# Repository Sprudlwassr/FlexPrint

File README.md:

\# Diploma thesis FlexPrint

This diploma thesis develops a modular CoreXY 3D printer that flexibly combines mechanics, electronics, and software and is designed for future extensions. The mechanical setup includes a Z-axis with four individually driven motors, linear rails, and a magnetically interchangeable toolhead system for different nozzle diameters. Electronically, a custom mainboard based on ESP32 or STM32 with TMC2209 stepper motor drivers is implemented. Control is provided via customized firmware (Klipper or Marlin). Extensions such as alternative toolheads, modular interfaces, and a secure power supply are integrated. The goal is a practical, reliable 3D printer that goes beyond commercial devices and serves as a platform for research and development.

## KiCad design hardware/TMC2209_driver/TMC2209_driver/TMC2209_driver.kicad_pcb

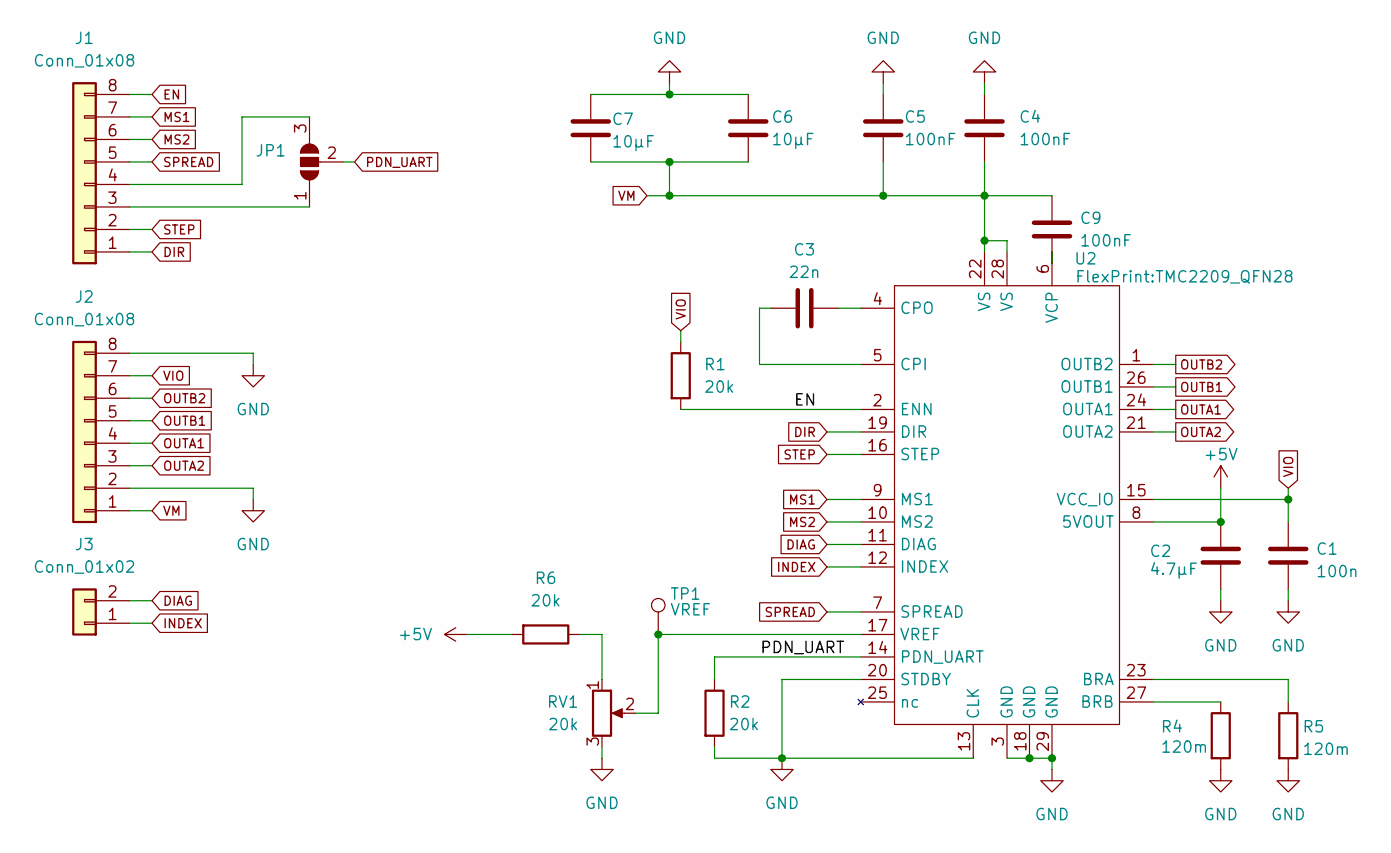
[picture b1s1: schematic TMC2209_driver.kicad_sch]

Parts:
C1: 100n; C_0402_1005Metric
C2: 4.7µF; C_0402_1005Metric
C3: 22n; C_0402_1005Metric
C4, C5, C9: 100nF; C_0402_1005Metric
C6, C7: 10µF; C_1206_3216Metric
J1, J2: Conn_01x08; PinHeader_1x08_P2.54mm_Vertical
J3: Conn_01x02; PinHeader_1x02_P2.54mm_Vertical
JP1: SolderJumper_3_Open; SolderJumper_3Pads
R1, R2, R6: 20k; R_0402_1005Metric
R4, R5: 120m; R_0805_2012Metric
RV1: 20k; TRIMMER_3312J-1-203E
TP1: VREF; TestPoint_Pad_D1.0mm
U2: TMC2209_QFN28

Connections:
+5V: C2.1, R6.2, U2.8 (5VOUT)
DIAG: J3.2, U2.11 (DIAG)
DIR: J1.1, U2.19 (DIR)
EN: J1.8, R1.2, U2.2 (ENN)
GND: C1.2, C2.2, C4.1, C5.1, C6.1, C7.1, J2.2, J2.8, R2.2, R4.2, R5.2, RV1.3, U2.3 (GND), U2.13 (CLK), U2.18 (GND), U2.20 (STDBY), U2.29 (GND)
INDEX: J3.1, U2.12 (INDEX)
MS1: J1.7, U2.9 (MS1)
MS2: J1.6, U2.10 (MS2)
unnamed: J1.3, JP1.1 (A)
unnamed: J1.4, JP1.3 (B)
unnamed: R6.1, RV1.1
unnamed: R5.1, U2.23 (BRA)
unnamed: R4.1, U2.27 (BRB)
unnamed: C3.1, U2.5 (CPI)
unnamed: C3.2, U2.4 (CPO)
unnamed: C9.2, U2.6 (VCP)
unnamed: RV1.2, TP1.1, U2.17 (VREF)
OUTA1: J2.4, U2.24 (OUTA1)
OUTA2: J2.3, U2.21 (OUTA2)
OUTB1: J2.5, U2.26 (OUTB1)
OUTB2: J2.6, U2.1 (OUTB2)
PDN_UART: JP1.2 (C), R2.1, U2.14 (PDN_UART)
SPREAD: J1.5, U2.7 (SPREAD)
STEP: J1.2, U2.16 (STEP)
VIO: C1.1, J2.7, R1.1, U2.15 (VCC_IO)
VM: C4.2, C5.2, C6.2, C7.2, C9.1, J2.1, U2.22 (VS), U2.28 (VS)

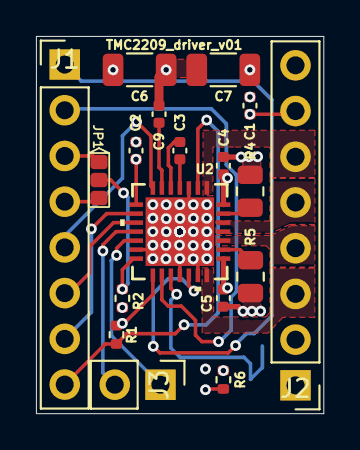
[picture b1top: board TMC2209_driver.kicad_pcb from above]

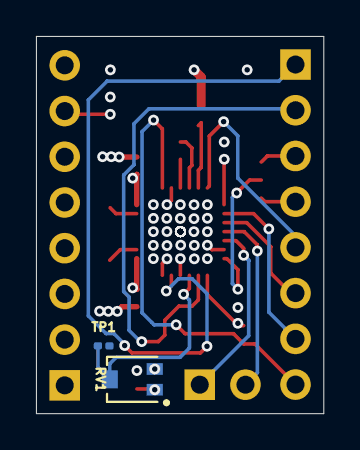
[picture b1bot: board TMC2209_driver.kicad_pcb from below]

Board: 4 copper layers, 16.0 x 21.0 mm, 20 parts (2 on the bottom side), 26 nets.

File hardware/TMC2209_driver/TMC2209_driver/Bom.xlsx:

Pos | Sourced | Placed | References | Value | Footprint | Stk | Stk Gesamt | Preis pro stk | Preis ab 10stk | Gesamtpreise | Anzahl Boards
1 | https://www.reichelt.at/at/de/shop/produkt/mlcc_0402_100nf_5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 | no | C3, C4, C5, C9 | 100nF | C_0402_1005Metric | 4 | 40 | 0.02 | 0.02 | 0.8 | 10
2 | https://www.reichelt.at/at/de/shop/produkt/mlcc_1206_10_f_35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 | no | C6, C7 | 10µF | C_1206_3216Metric | 2 | 20 | 0.08 | 0.08 | 1.6
3 | https://www.reichelt.at/at/de/shop/produkt/mlcc_0402_4_7uf_1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 | no | C2 | 4.7µF | C_0402_1005Metric | 1 | 10 | 0.03 | 0.03 | 0.3
4 | https://www.reichelt.at/at/de/shop/produkt/mlcc_0402_22nf_50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 | no | C3 | 22n | C_0402_1005Metric | 1 | 10 | 0.02 | 0.02 | 0.2
5 | https://www.reichelt.at/at/de/shop/produkt/smd-widerstand_04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 | no | R1, R2, R6 | 20k | R_0402_1005Metric | 3 | 30 | 0.02 | 0.02 | 0.6
6 | https://www.mouser.at/ProductDetail/Panasonic/ERJ-6BSFR12V?q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 | no | R4, R5 | 120m | R_0805_2012Metric | 2 | 20 | 0.24099999999999999 | 0.155 | 3.1
7 | https://www.reichelt.at/at/de/shop/produkt/tmc2209_schrittmo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 | no | U2 | ~ | TMC2209_QFN28 | 1 | 10 | 3.33 | 3.33 | 33.299999999999997
8 | https://www.mouser.at/ProductDetail/Bourns/TC42X-2-203E?qs=A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 | no | RV1 | 20k | TC42X-2-203E | 1 | 10 | 0.38700000000000001 | 0.28999999999999998 | 2.9
9 |  | no | J1, J2 | Conn_01x08 | PinHeader_1x08_P2.54mm_Vertical | 2 | 20
10 |  | no | J3 | Conn_01x02 | PinHeader_1x02_P2.54mm_Vertical | 1 | 10
 |  |  |  |  |  |  |  |  | Summe | 42.8

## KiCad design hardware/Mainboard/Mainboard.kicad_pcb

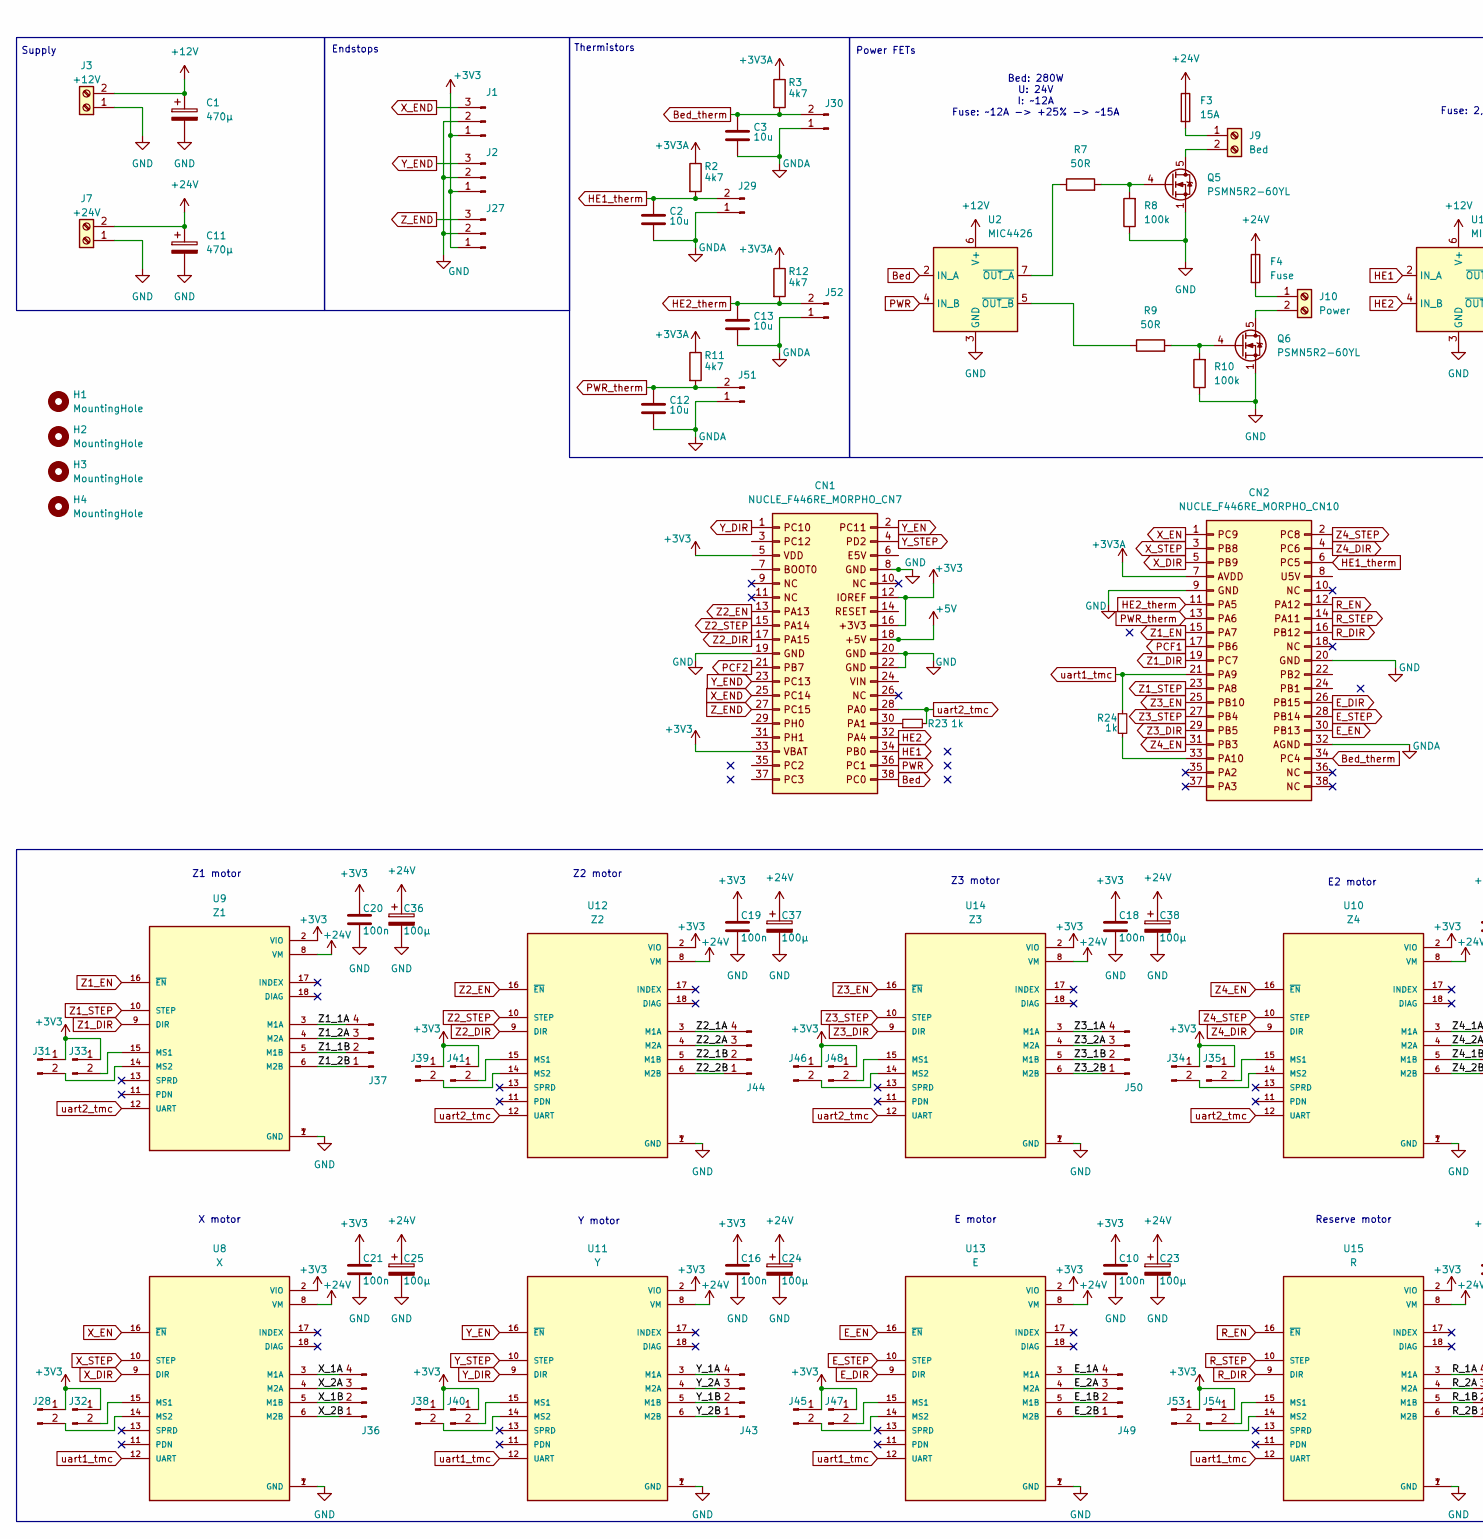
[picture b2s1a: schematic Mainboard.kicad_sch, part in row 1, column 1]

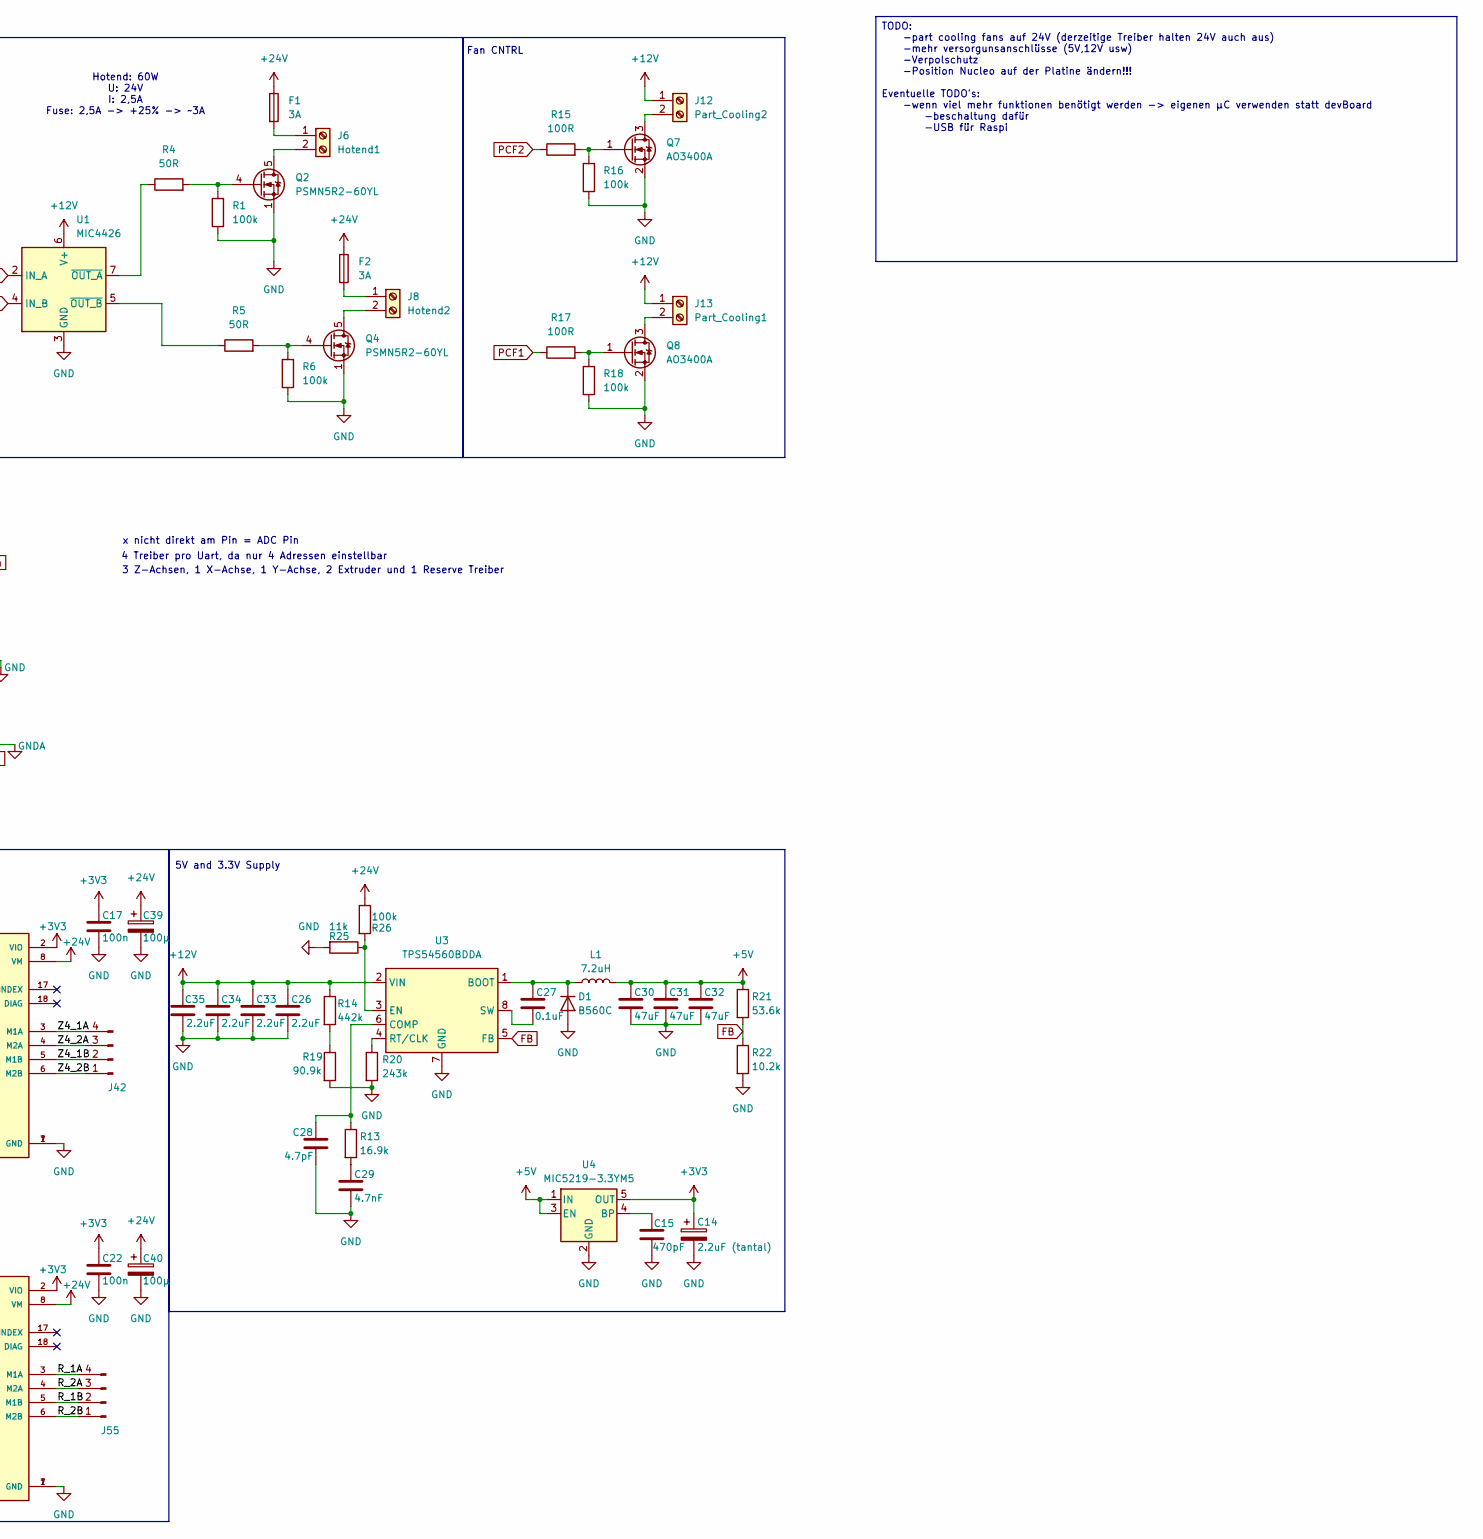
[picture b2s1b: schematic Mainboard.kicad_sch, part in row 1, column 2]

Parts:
C1, C11: 470µ; CP_Elec_16x17.5
C2, C3, C12, C13: 10u; C_0805_2012Metric
C10, C16, C17, C18, C19, C20, C21, C22: 100n; C_0805_2012Metric
C14: 2.2uF (tantal); CP_EIA-3216-10_Kemet-I
C15: 470pF; C_0805_2012Metric
C23, C24, C25, C36, C37, C38, C39, C40: 100µ; CP_Elec_8x10
C26, C33, C34, C35: 2.2uF; C_0805_2012Metric
C27: 0.1uF; C_0805_2012Metric
C28: 4.7pF; C_0805_2012Metric
C29: 4.7nF; C_0805_2012Metric
C30, C31, C32: 47uF; C_0805_2012Metric
CN1: NUCLE_F446RE_MORPHO_CN7; PinSocket_2x19_P2.54mm_Vertical
CN2: NUCLE_F446RE_MORPHO_CN10; PinSocket_2x19_P2.54mm_Vertical
D1: B560C; D_SMC
F1, F2: 3A; Fuse_1206_3216Metric
F3: 15A; Fuse_1206_3216Metric
F4: Fuse; Fuse_1206_3216Metric
H1, H2, H3, H4: MountingHole; MountingHole_2.7mm_M2.5_Pad_Via
J1: X_END; JST_XH_B3B-XH-A_1x03_P2.50mm_Vertical
J2: Y_END; JST_XH_B3B-XH-A_1x03_P2.50mm_Vertical
J3: +12V; TerminalBlock_bornier-2_P5.08mm
J6: Hotend1; TerminalBlock_bornier-2_P5.08mm
J7: +24V; TerminalBlock_bornier-2_P5.08mm
J8: Hotend2; TerminalBlock_bornier-2_P5.08mm
J9: Bed; TerminalBlock_bornier-2_P5.08mm
J10: Power; TerminalBlock_bornier-2_P5.08mm
J12: Part_Cooling2; JST_XH_B2B-XH-A_1x02_P2.50mm_Vertical
J13: Part_Cooling1; JST_XH_B2B-XH-A_1x02_P2.50mm_Vertical
J27: Z_END; JST_XH_B3B-XH-A_1x03_P2.50mm_Vertical
J28: X_MS2; PinHeader_1x02_P2.54mm_Vertical
J29: HE1_therm; JST_XH_B2B-XH-A_1x02_P2.50mm_Vertical
J30: Bed_therm; JST_XH_B2B-XH-A_1x02_P2.50mm_Vertical
J31: Z1_MS2; PinHeader_1x02_P2.54mm_Vertical
J32: X_MS1; PinHeader_1x02_P2.54mm_Vertical
J33: Z1_MS1; PinHeader_1x02_P2.54mm_Vertical
J34: Z4_MS2; PinHeader_1x02_P2.54mm_Vertical
J35: Z4_MS1; PinHeader_1x02_P2.54mm_Vertical
J36: X_Motor; PinHeader_1x04_P2.54mm_Vertical
J37: Z1_Motor; PinHeader_1x04_P2.54mm_Vertical
J38: Y_MS2; PinHeader_1x02_P2.54mm_Vertical
J39: Z2_MS2; PinHeader_1x02_P2.54mm_Vertical
J40: Y_MS1; PinHeader_1x02_P2.54mm_Vertical
J41: Z2_MS1; PinHeader_1x02_P2.54mm_Vertical
J42: Z4_Motor; PinHeader_1x04_P2.54mm_Vertical
J43: Y_Motor; PinHeader_1x04_P2.54mm_Vertical
J44: Z2_Motor; PinHeader_1x04_P2.54mm_Vertical
J45: E_MS2; PinHeader_1x02_P2.54mm_Vertical
J46: Z3_MS2; PinHeader_1x02_P2.54mm_Vertical
J47: E_MS1; PinHeader_1x02_P2.54mm_Vertical
J48: Z3_MS1; PinHeader_1x02_P2.54mm_Vertical
J49: E_Motor; PinHeader_1x04_P2.54mm_Vertical
J50: Z3_Motor; PinHeader_1x04_P2.54mm_Vertical
J51: PWR_therm; JST_XH_B2B-XH-A_1x02_P2.50mm_Vertical
J52: HE2_therm; JST_XH_B2B-XH-A_1x02_P2.50mm_Vertical
J53: R_MS2; PinHeader_1x02_P2.54mm_Vertical
J54: R_MS1; PinHeader_1x02_P2.54mm_Vertical
J55: R_Motor; PinHeader_1x04_P2.54mm_Vertical
L1: 7.2uH; L_Wuerth_WE-PDF
Q2, Q4, Q5, Q6: PSMN5R2-60YL; LFPAK56
Q7, Q8: AO3400A; SOT-23
R1, R6, R8, R10, R16, R18, R26: 100k; R_0805_2012Metric
R2, R3, R11, R12: 4k7; R_0805_2012Metric
R4, R5, R7, R9: 50R; R_0805_2012Metric
R13: 16.9k; R_0805_2012Metric
R14: 442k; R_0805_2012Metric
R15, R17: 100R; R_0805_2012Metric
R19: 90.9k; R_0805_2012Metric
R20: 243k; R_0805_2012Metric
R21: 53.6k; R_0805_2012Metric
R22: 10.2k; R_0805_2012Metric
R23, R24: 1k; R_0805_2012Metric
R25: 11k; R_0805_2012Metric
U1, U2: MIC4426; SOIC-8_3.9x4.9mm_P1.27mm
U3: TPS54560BDDA; Texas_R-PDSO-G8_EP2.95x4.9mm_Mask2.4x3.1mm_ThermalVias
U4: MIC5219-3.3YM5; SOT-23-5
U8: X; MODULE_TMC2209_SILENTSTEPSTICK; PARTREV 1.20
U9: Z1; MODULE_TMC2209_SILENTSTEPSTICK; PARTREV 1.20
U10: Z4; MODULE_TMC2209_SILENTSTEPSTICK; PARTREV 1.20
U11: Y; MODULE_TMC2209_SILENTSTEPSTICK; PARTREV 1.20
U12: Z2; MODULE_TMC2209_SILENTSTEPSTICK; PARTREV 1.20
U13: E; MODULE_TMC2209_SILENTSTEPSTICK; PARTREV 1.20
U14: Z3; MODULE_TMC2209_SILENTSTEPSTICK; PARTREV 1.20
U15: R; MODULE_TMC2209_SILENTSTEPSTICK; PARTREV 1.20

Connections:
+3V3: C10.1, C14.1, C16.1, C17.1, C18.1, C19.1, C20.1, C21.1, C22.1, CN1.5, CN1.12, CN1.16, CN1.33, J1.1, J2.1, J27.1, J28.1, J31.1, J32.1, J33.1, J34.1, J35.1, J38.1, J39.1, J40.1, J41.1, J45.1, J46.1, J47.1, J48.1, J53.1, J54.1, U4.5 (OUT), U8.2 (VIO), U9.2 (VIO), U10.2 (VIO), U11.2 (VIO), U12.2 (VIO), U13.2 (VIO), U14.2 (VIO), U15.2 (VIO)
+3V3A: CN2.7, R2.1, R3.1, R11.1, R12.1
+5V: C30.1, C31.1, C32.1, CN1.18, L1.2, R21.1, U4.1 (IN), U4.3 (EN)
+12V: C1.1, C26.1, C33.1, C34.1, C35.1, J3.2, J12.1, J13.1, R14.1, U1.6 (V+), U2.6 (V+), U3.2 (VIN)
+24V: C11.1, C23.1, C24.1, C25.1, C36.1, C37.1, C38.1, C39.1, C40.1, F1.1, F2.1, F3.1, F4.1, J7.2, R26.1, U8.8 (VM), U9.8 (VM), U10.8 (VM), U11.8 (VM), U12.8 (VM), U13.8 (VM), U14.8 (VM), U15.8 (VM)
/E_1A: J49.4, U13.3 (M1A)
/E_1B: J49.2, U13.5 (M1B)
/E_2A: J49.3, U13.4 (M2A)
/E_2B: J49.1, U13.6 (M2B)
/R_1A: J55.4, U15.3 (M1A)
/R_1B: J55.2, U15.5 (M1B)
/R_2A: J55.3, U15.4 (M2A)
/R_2B: J55.1, U15.6 (M2B)
/X_1A: J36.4, U8.3 (M1A)
/X_1B: J36.2, U8.5 (M1B)
/X_2A: J36.3, U8.4 (M2A)
/X_2B: J36.1, U8.6 (M2B)
/Y_1A: J43.4, U11.3 (M1A)
/Y_1B: J43.2, U11.5 (M1B)
/Y_2A: J43.3, U11.4 (M2A)
/Y_2B: J43.1, U11.6 (M2B)
/Z1_1A: J37.4, U9.3 (M1A)
/Z1_1B: J37.2, U9.5 (M1B)
/Z1_2A: J37.3, U9.4 (M2A)
/Z1_2B: J37.1, U9.6 (M2B)
/Z2_1A: J44.4, U12.3 (M1A)
/Z2_1B: J44.2, U12.5 (M1B)
/Z2_2A: J44.3, U12.4 (M2A)
/Z2_2B: J44.1, U12.6 (M2B)
/Z3_1A: J50.4, U14.3 (M1A)
/Z3_1B: J50.2, U14.5 (M1B)
/Z3_2A: J50.3, U14.4 (M2A)
/Z3_2B: J50.1, U14.6 (M2B)
/Z4_1A: J42.4, U10.3 (M1A)
/Z4_1B: J42.2, U10.5 (M1B)
/Z4_2A: J42.3, U10.4 (M2A)
/Z4_2B: J42.1, U10.6 (M2B)
Bed: CN1.38, U2.2 (IN_A)
Bed_therm: C3.1, CN2.34, J30.2, R3.2
E_DIR: CN2.26, U13.9 (DIR)
E_EN: CN2.30, U13.16 (~EN)
E_STEP: CN2.28, U13.10 (STEP)
FB: R21.2, R22.1, U3.5 (FB)
GND: C1.2, C10.2, C11.2, C14.2, C15.2, C16.2, C17.2, C18.2, C19.2, C20.2, C21.2, C22.2, C23.2, C24.2, C25.2, C26.2, C28.2, C29.2, C30.2, C31.2, C32.2, C33.2, C34.2, C35.2, C36.2, C37.2, C38.2, C39.2, C40.2, CN1.8, CN1.19, CN1.20, CN1.22, CN2.9, CN2.20, D1.2 (A), J1.2, J2.2, J3.1, J7.1, J27.2, Q2.1 (S), Q2.2 (S), Q2.3 (S), Q4.1 (S), Q4.2 (S), Q4.3 (S), Q5.1 (S), Q5.2 (S), Q5.3 (S), Q6.1 (S), Q6.2 (S), Q6.3 (S), Q7.2 (S), Q8.2 (S), R1.1, R6.1, R8.1, R10.1, R16.1, R18.1, R19.2, R20.2, R22.2, R25.2, U1.3 (GND), U2.3 (GND), U3.7 (GND), U3.9 (GND), U4.2 (GND), U8.1 (GND), U8.7 (GND), U9.1 (GND), U9.7 (GND), U10.1 (GND), U10.7 (GND), U11.1 (GND), U11.7 (GND), U12.1 (GND), U12.7 (GND), U13.1 (GND), U13.7 (GND), U14.1 (GND), U14.7 (GND), U15.1 (GND), U15.7 (GND)
GNDA: C2.2, C3.2, C12.2, C13.2, CN2.32, J29.1, J30.1, J51.1, J52.1
HE1: CN1.34, U1.2 (IN_A)
HE1_therm: C2.1, CN2.6, J29.2, R2.2
HE2: CN1.32, U1.4 (IN_B)
HE2_therm: C13.1, CN2.11, J52.2, R12.2
unnamed: C29.1, R13.2
unnamed: CN1.30, R23.1
unnamed: CN2.33, R24.2
unnamed: C27.1, D1.1 (K), L1.1, U3.1 (BOOT)
unnamed: F1.2, J6.1
unnamed: J6.2, Q2.5 (D)
unnamed: F2.2, J8.1
unnamed: J8.2, Q4.5 (D)
unnamed: F3.2, J9.1
unnamed: J9.2, Q5.5 (D)
unnamed: F4.2, J10.1
unnamed: J10.2, Q6.5 (D)
unnamed: J12.2, Q7.3 (D)
unnamed: J13.2, Q8.3 (D)
unnamed: J28.2, U8.14 (MS2)
unnamed: J31.2, U9.14 (MS2)
unnamed: J32.2, U8.15 (MS1)
unnamed: J33.2, U9.15 (MS1)
unnamed: J34.2, U10.14 (MS2)
unnamed: J35.2, U10.15 (MS1)
unnamed: J38.2, U11.14 (MS2)
unnamed: J39.2, U12.14 (MS2)
unnamed: J40.2, U11.15 (MS1)
unnamed: J41.2, U12.15 (MS1)
unnamed: J45.2, U13.14 (MS2)
unnamed: J46.2, U14.14 (MS2)
unnamed: J47.2, U13.15 (MS1)
unnamed: J48.2, U14.15 (MS1)
unnamed: J53.2, U15.14 (MS2)
unnamed: J54.2, U15.15 (MS1)
unnamed: Q2.4 (G), R1.2, R4.2
unnamed: Q4.4 (G), R5.2, R6.2
unnamed: Q5.4 (G), R7.2, R8.2
unnamed: Q6.4 (G), R9.2, R10.2
unnamed: Q7.1 (G), R15.2, R16.2
unnamed: Q8.1 (G), R17.2, R18.2
unnamed: R14.2, R19.1
unnamed: R4.1, U1.7 (~OUT_A)
unnamed: R5.1, U1.5 (~OUT_B)
unnamed: R7.1, U2.7 (~OUT_A)
unnamed: R9.1, U2.5 (~OUT_B)
unnamed: C28.1, R13.1, U3.6 (COMP)
unnamed: R25.1, R26.2, U3.3 (EN)
unnamed: R20.1, U3.4 (RT/CLK)
unnamed: C27.2, U3.8 (SW)
unnamed: C15.1, U4.4 (BP)
PCF1: CN2.17, R17.1
PCF2: CN1.21, R15.1
PWR: CN1.36, U2.4 (IN_B)
PWR_therm: C12.1, CN2.13, J51.2, R11.2
R_DIR: CN2.16, U15.9 (DIR)
R_EN: CN2.12, U15.16 (~EN)
R_STEP: CN2.14, U15.10 (STEP)
X_DIR: CN2.5, U8.9 (DIR)
X_EN: CN2.1, U8.16 (~EN)
X_END: CN1.25, J1.3
X_STEP: CN2.3, U8.10 (STEP)
Y_DIR: CN1.1, U11.9 (DIR)
Y_EN: CN1.2, U11.16 (~EN)
Y_END: CN1.23, J2.3
Y_STEP: CN1.4, U11.10 (STEP)
Z1_DIR: CN2.19, U9.9 (DIR)
Z1_EN: CN2.15, U9.16 (~EN)
Z1_STEP: CN2.23, U9.10 (STEP)
Z2_DIR: CN1.17, U12.9 (DIR)
Z2_EN: CN1.13, U12.16 (~EN)
Z2_STEP: CN1.15, U12.10 (STEP)
Z3_DIR: CN2.29, U14.9 (DIR)
Z3_EN: CN2.25, U14.16 (~EN)
Z3_STEP: CN2.27, U14.10 (STEP)
Z4_DIR: CN2.4, U10.9 (DIR)
Z4_EN: CN2.31, U10.16 (~EN)
Z4_STEP: CN2.2, U10.10 (STEP)
Z_END: CN1.27, J27.3
uart1_tmc: CN2.21, R24.1, U8.12 (UART), U11.12 (UART), U13.12 (UART), U15.12 (UART)
uart2_tmc: CN1.28, R23.2, U9.12 (UART), U10.12 (UART), U12.12 (UART), U14.12 (UART)

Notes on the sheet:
x nicht direkt am Pin = ADC Pin
Y motor
5V and 3.3V Supply
Hotend: 60W U: 24V I: 2,5A Fuse: 2,5A -> +25% -> ~3A
Reserve motor
Z3 motor
Supply
Z2 motor
E motor
Endstops
E2 motor
Bed: 280W U: 24V I: ~12A Fuse: ~12A -> +25% -> ~15A
4 Treiber pro Uart, da nur 4 Adressen einstellbar
Power FETs
Thermistors
Fan CNTRL
Z1 motor
3 Z-Achsen, 1 X-Achse, 1 Y-Achse, 2 Extruder und 1 Reserve Treiber
X motor
TODO: -part cooling fans auf 24V (derzeitige Treiber halten 24V auch aus) -mehr versorgunsanschlüsse (5V,12V usw) -Verpolschutz -Position Nucleo auf der Platine ändern!!! Eventuelle TODO's: -wenn viel mehr funktionen benötigt werden -> eigenen µC verwenden statt devBoard -beschaltung dafür -USB für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

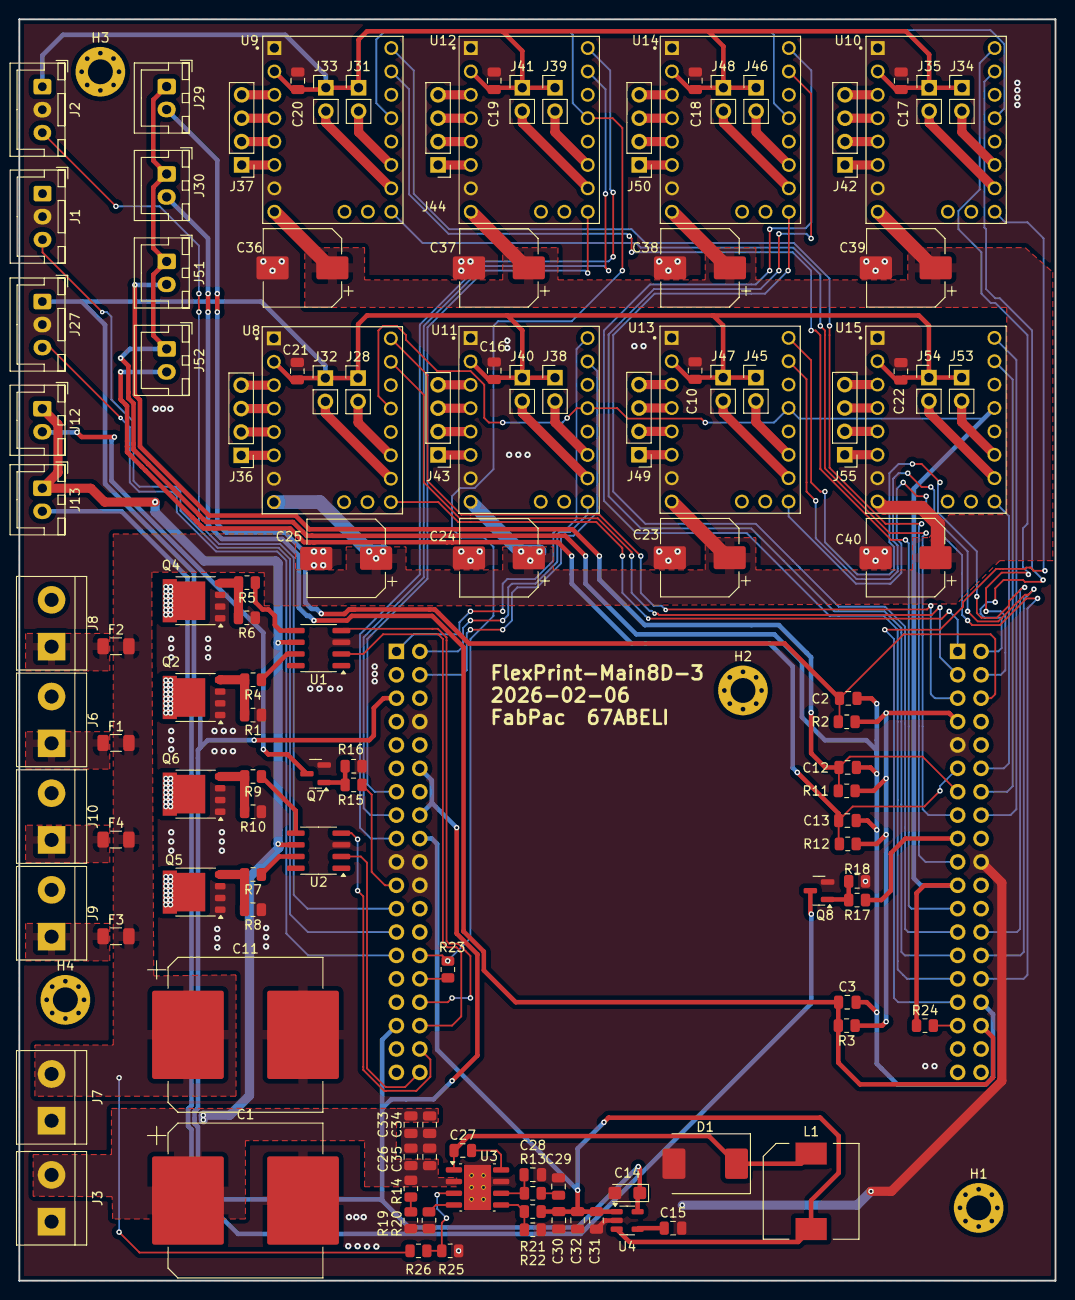
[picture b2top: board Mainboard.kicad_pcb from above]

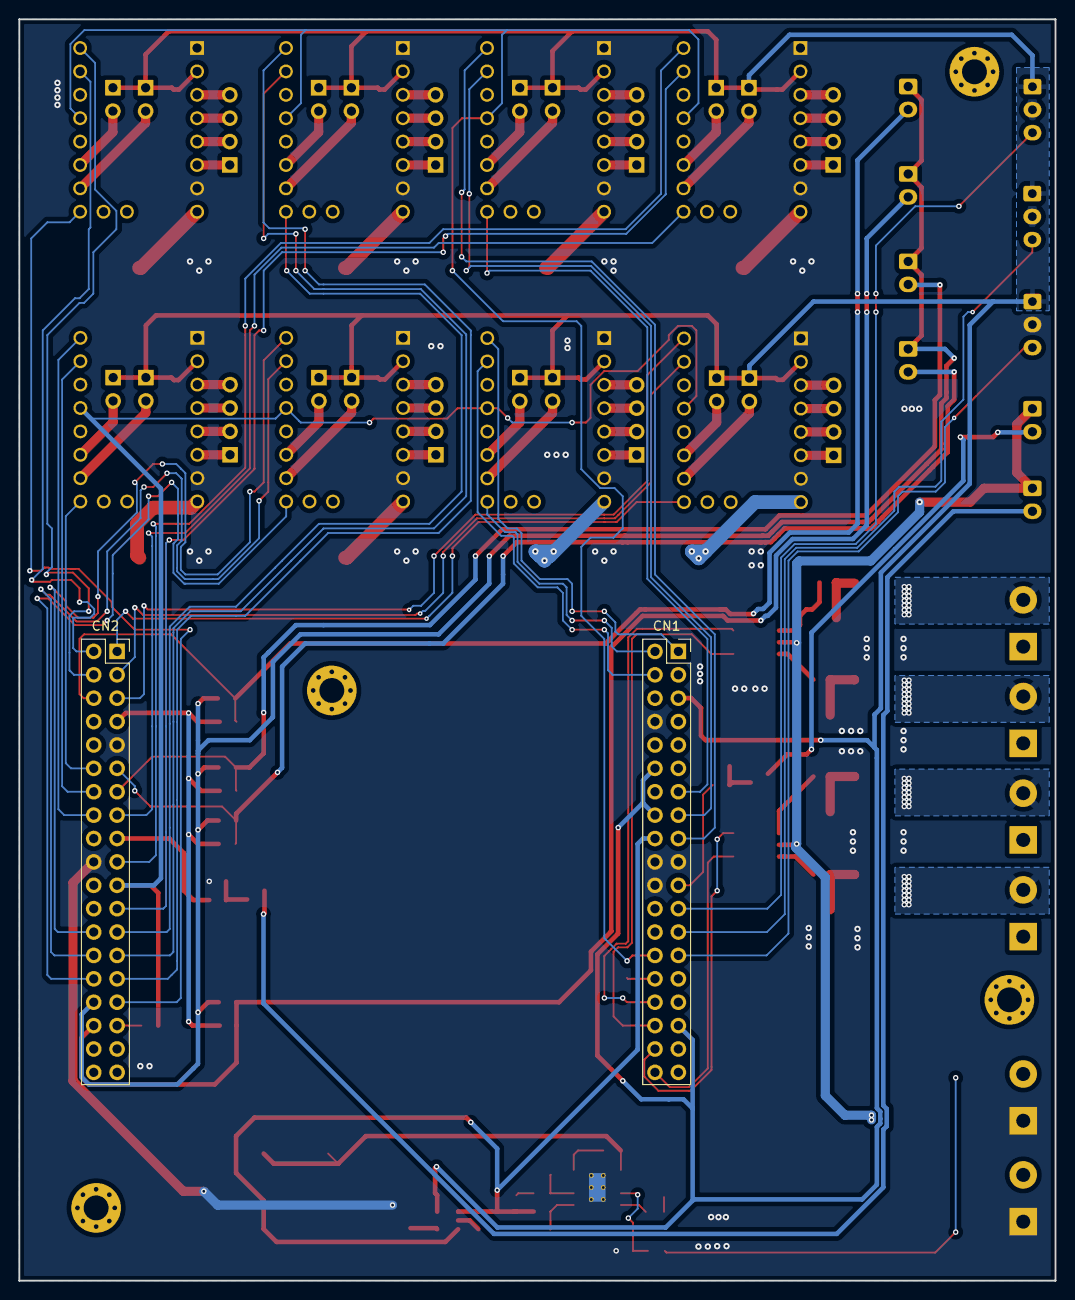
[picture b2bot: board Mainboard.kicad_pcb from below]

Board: 2 copper layers, 112.5 x 137.0 mm, 129 parts (2 on the bottom side), 125 nets.

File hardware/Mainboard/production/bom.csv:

Designator,Footprint,Quantity,Value,LCSC Part #
"C1, C11",CP_Elec_16x17.5,2,470µ,
"C10, C16, C17, C18, C19, C20, C21, C22",0805,8,100n,
"C12, C13, C2, C3",0805,4,10u,
C14,CP_EIA-3216-10_Kemet-I,1,2.2uF (tantal),
C15,0805,1,470pF,
"C23, C24, C25, C36, C37, C38, C39, C40",CP_Elec_8x10,8,100µ,
"C26, C33, C34, C35",0805,4,2.2uF,
C27,0805,1,0.1uF,
C28,0805,1,4.7pF,
C29,0805,1,4.7nF,
"C30, C31, C32",0805,3,47uF,
CN1,PinSocket_2x19_P2.54mm_Vertical,1,NUCLE_F446RE_MORPHO_CN7,
CN2,PinSocket_2x19_P2.54mm_Vertical,1,NUCLE_F446RE_MORPHO_CN10,
D1,D_SMC,1,B560C,
"F1, F2",1206,2,3A,
F3,1206,1,15A,
F4,1206,1,Fuse,
J1,JST_XH_B3B-XH-A_1x03_P2.50mm_Vertical,1,X_END,
J10,TerminalBlock_bornier-2_P5.08mm,1,Power,
J12,JST_XH_B2B-XH-A_1x02_P2.50mm_Vertical,1,Part_Cooling2,
J13,JST_XH_B2B-XH-A_1x02_P2.50mm_Vertical,1,Part_Cooling1,
J2,JST_XH_B3B-XH-A_1x03_P2.50mm_Vertical,1,Y_END,
J27,JST_XH_B3B-XH-A_1x03_P2.50mm_Vertical,1,Z_END,
J28,PinHeader_1x02_P2.54mm_Vertical,1,X_MS2,
J29,JST_XH_B2B-XH-A_1x02_P2.50mm_Vertical,1,HE1_therm,
J3,TerminalBlock_bornier-2_P5.08mm,1,+12V,
J30,JST_XH_B2B-XH-A_1x02_P2.50mm_Vertical,1,Bed_therm,
J31,PinHeader_1x02_P2.54mm_Vertical,1,Z1_MS2,
J32,PinHeader_1x02_P2.54mm_Vertical,1,X_MS1,
J33,PinHeader_1x02_P2.54mm_Vertical,1,Z1_MS1,
J34,PinHeader_1x02_P2.54mm_Vertical,1,Z4_MS2,
J35,PinHeader_1x02_P2.54mm_Vertical,1,Z4_MS1,
J36,PinHeader_1x04_P2.54mm_Vertical,1,X_Motor,
J37,PinHeader_1x04_P2.54mm_Vertical,1,Z1_Motor,
J38,PinHeader_1x02_P2.54mm_Vertical,1,Y_MS2,
J39,PinHeader_1x02_P2.54mm_Vertical,1,Z2_MS2,
J40,PinHeader_1x02_P2.54mm_Vertical,1,Y_MS1,
J41,PinHeader_1x02_P2.54mm_Vertical,1,Z2_MS1,
J42,PinHeader_1x04_P2.54mm_Vertical,1,Z4_Motor,
J43,PinHeader_1x04_P2.54mm_Vertical,1,Y_Motor,
J44,PinHeader_1x04_P2.54mm_Vertical,1,Z2_Motor,
J45,PinHeader_1x02_P2.54mm_Vertical,1,E_MS2,
J46,PinHeader_1x02_P2.54mm_Vertical,1,Z3_MS2,
J47,PinHeader_1x02_P2.54mm_Vertical,1,E_MS1,
J48,PinHeader_1x02_P2.54mm_Vertical,1,Z3_MS1,
J49,PinHeader_1x04_P2.54mm_Vertical,1,E_Motor,
J50,PinHeader_1x04_P2.54mm_Vertical,1,Z3_Motor,
J51,JST_XH_B2B-XH-A_1x02_P2.50mm_Vertical,1,PWR_therm,
J52,JST_XH_B2B-XH-A_1x02_P2.50mm_Vertical,1,HE2_therm,
J53,PinHeader_1x02_P2.54mm_Vertical,1,R_MS2,
J54,PinHeader_1x02_P2.54mm_Vertical,1,R_MS1,
J55,PinHeader_1x04_P2.54mm_Vertical,1,R_Motor,
J6,TerminalBlock_bornier-2_P5.08mm,1,Hotend1,
J7,TerminalBlock_bornier-2_P5.08mm,1,+24V,
J8,TerminalBlock_bornier-2_P5.08mm,1,Hotend2,
J9,TerminalBlock_bornier-2_P5.08mm,1,Bed,
L1,L_Wuerth_WE-PDF,1,7.2uH,
"Q2, Q4, Q5, Q6",LFPAK56,4,PSMN5R2-60YL,
"Q7, Q8",SOT-23,2,AO3400A,
"R1, R10, R16, R18, R26, R6, R8",0805,7,100k,
"R11, R12, R2, R3",0805,4,4k7,
R13,0805,1,16.9k,
R14,0805,1,442k,
"R15, R17",0805,2,100R,
R19,0805,1,90.9k,
R20,0805,1,243k,
R21,0805,1,53.6k,
R22,0805,1,10.2k,
"R23, R24",0805,2,1k,
R25,0805,1,11k,
"R4, R5, R7, R9",0805,4,50R,
"U1, U2",SOIC-8_3.9x4.9mm_P1.27mm,2,MIC4426,
U10,MODULE_TMC2209_SILENTSTEPSTICK,1,Z4,
U11,MODULE_TMC2209_SILENTSTEPSTICK,1,Y,
U12,MODULE_TMC2209_SILENTSTEPSTICK,1,Z2,
U13,MODULE_TMC2209_SILENTSTEPSTICK,1,E,
U14,MODULE_TMC2209_SILENTSTEPSTICK,1,Z3,
U15,MODULE_TMC2209_SILENTSTEPSTICK,1,R,
U3,Texas_R-PDSO-G8_EP2.95x4.9mm_Mask2.4x3.1mm_ThermalVias,1,TPS54560BDDA,
U4,SOT-23-5,1,MIC5219-3.3YM5,
U8,MODULE_TMC2209_SILENTSTEPSTICK,1,X,
U9,MODULE_TMC2209_SILENTSTEPSTICK,1,Z1,

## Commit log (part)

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2025-09-19 Blockschaltbild-Konzept hinzugefügt
2025-09-20 20.09.2025 BOM hinzugefügt
2025-09-20 added a few graphs
2025-09-21 21.09.2025 User Interface Blockschaltbild
2025-09-28 updated mainboard schematics
2025-09-28 Software Doku added
2025-09-28 added other files
    mainly netzteil
2025-10-26 driver board for TMC2209
2025-12-04 finished driver board design
2025-12-05 Software Update
2025-12-05 driver board finalized, mainboard started placing FET drivers
2025-12-12 Mainboard changes + BOM for Driver
2026-02-06 Mainboard-3
    Version 3 of Mainboard, (version 2 not uploaded)
2026-02-20 Software Update 20.02.26 8:05-9:30
2026-02-28 Printer.cfg Backup + Softwaredoku Update
2026-03-06 Code Update
    HTML Implementation in React
2026-03-07 Widgets (nicht funktionsfähig)
    Evtl. kann er die Dateien nicht richtig aufrufen
2026-03-14 mainboard v2
2026-03-14 Flexprint Functional Widgets
2026-03-27 Fixed Widget Dashboard
2026-03-27 graphics/logo
2026-04-11 Software Update 11.04.2026 10:03
2026-04-17 Tailwind eingebunden
2026-04-17 Ordnerstruktur eingerichtet
2026-04-24 Grundgerüst fertiggestellt
2026-04-25 Moonraker hinzugefüfgt
2026-04-25 Update Pi Temperature
2026-05-07 changed ip address
2026-05-08 Software log added / ip change
2026-06-08 3d files and documentation
2026-06-09 Doku weitergemacht
